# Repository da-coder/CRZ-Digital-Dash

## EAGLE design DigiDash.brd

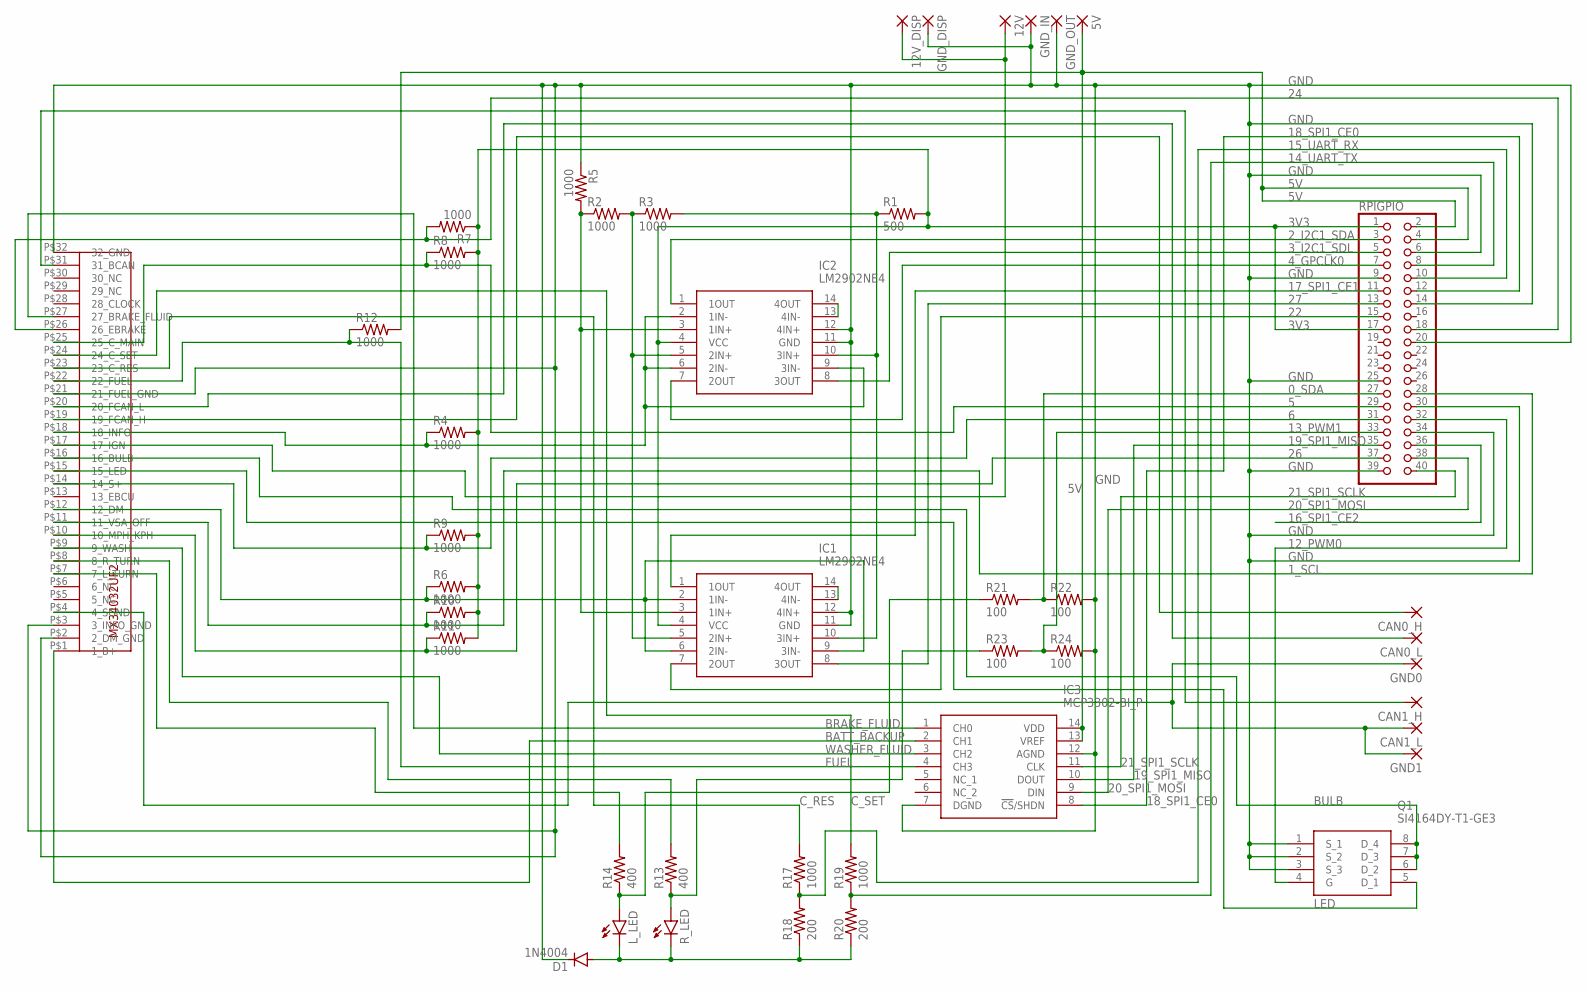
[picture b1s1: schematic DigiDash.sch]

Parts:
5V, 12V, 12V_DISP: 3,81/1,4
CAN0_H, CAN0_L, CAN1_H, CAN1_L: 3,81/1,4
D1: 1N4004; DO41-10
GND0, GND1: 3,81/1,4
GND_DISP: 3,81/1,4
GND_IN: 3,81/1,4
GND_OUT: 3,81/1,4
IC1, IC2: LM2902NE4; DIP794W53P254L1930H508Q14N
IC3: MCP3302-BI_P; DIP781W56P254L1918H533Q14N
L_LED: LED3MM
Q1: SI4164DY-T1-GE3; SOIC127P600X175-8N
R1: 500; 0204/7
R2, R3, R4, R5, R6, R7, R8, R9, R10, R11, R12, R17, R19: 1000; 0204/7
R13, R14: 400; 0204/7
R18, R20: 200; 0204/7
R21, R22, R23, R24: 100; 0204/7
RPIGPIO: PINHD-2X20; 2X20
R_LED: LED3MM
U$1: MX34032UF2

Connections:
0_SDA: R21.2, R22.1, RPIGPIO.27
1_SCL: R10.1, RPIGPIO.28, U$1.P$11 (11_VSA_OFF)
2_I2C1_SDA: IC2.1 (1OUT), RPIGPIO.3
3V3: IC1.4 (VCC), IC2.4 (VCC), R1.2, R4.2, R6.2, R7.1, R8.2, R9.2, R10.2, R11.2, RPIGPIO.1, RPIGPIO.17
3_I2C1_SDL: IC2.8 (3OUT), RPIGPIO.5
4_GPCLK0: IC2.7 (2OUT), RPIGPIO.7
5: R8.1, RPIGPIO.29, U$1.P$25 (25_C_MAIN)
5V: 5V.1, IC3.13 (VREF), IC3.14 (VDD), R12.2, RPIGPIO.2, RPIGPIO.4
6: R9.1, RPIGPIO.31, U$1.P$14 (14_S+)
12_PWM0: Q1.4 (G), RPIGPIO.32
13_PWM1: R23.2, R24.1, RPIGPIO.33
14_UART_TX: R19.1, R20.2, RPIGPIO.8
15_UART_RX: R17.1, R18.2, RPIGPIO.10
16_SPI1_CE2: RPIGPIO.36
17_SPI1_CE1: IC1.1 (1OUT), RPIGPIO.11
18_SPI1_CE0: IC3.8 (!CS!/SHDN), RPIGPIO.12
19_SPI1_MISO: IC3.10 (DOUT), RPIGPIO.35
20_SPI1_MOSI: IC3.9 (DIN), RPIGPIO.38
21_SPI1_SCLK: IC3.11 (CLK), RPIGPIO.40
22: IC1.7 (2OUT), RPIGPIO.15
24: R7.2, RPIGPIO.18, U$1.P$26 (26_EBRAKE)
26: R11.1, RPIGPIO.37, U$1.P$10 (10_MPH_KPH)
27: IC1.8 (3OUT), RPIGPIO.13
BATT_BACKUP: IC3.2 (CH1), U$1.P$1 (1_B+)
BRAKE_FLUID: IC3.1 (CH0), U$1.P$27 (27_BRAKE_FLUID)
BULB: Q1.6 (D_2), Q1.7 (D_3), Q1.8 (D_4), U$1.P$16 (16_BULB)
C_RES: R17.2, U$1.P$23 (23_C_RES)
C_SET: R19.2, U$1.P$24 (24_C_SET)
FUEL: IC3.4 (CH3), R12.1, U$1.P$22 (22_FUEL)
GND: D1.C, GND_DISP.1, GND_IN.1, GND_OUT.1, IC1.11 (GND), IC1.12 (4IN+), IC2.11 (GND), IC2.12 (4IN+), IC3.7 (DGND), IC3.12 (AGND), Q1.1 (S_1), Q1.2 (S_2), Q1.3 (S_3), R5.1, R22.2, R24.2, RPIGPIO.6, RPIGPIO.9, RPIGPIO.14, RPIGPIO.20, RPIGPIO.25, RPIGPIO.30, RPIGPIO.34, RPIGPIO.39, U$1.P$2 (2_DM_GND), U$1.P$3 (3_INFO_GND), U$1.P$21 (21_FUEL_GND), U$1.P$32 (32_GND)
LED: Q1.5 (D_1), U$1.P$15 (15_LED)
unnamed: IC1.2 (1IN-), IC1.6 (2IN-), IC1.9 (3IN-), R6.1, U$1.P$12 (12_DM)
unnamed: R14.2, U$1.P$7 (7_L_TURN)
unnamed: IC1.10 (3IN+), IC2.10 (3IN+), R1.1, R3.2
unnamed: IC1.3 (1IN+), IC2.3 (1IN+), R2.1, R5.2
unnamed: IC2.13 (4IN-), IC2.14 (4OUT)
unnamed: IC1.5 (2IN+), IC2.5 (2IN+), R2.2, R3.1
unnamed: IC1.13 (4IN-), IC1.14 (4OUT)
unnamed: CAN1_H.1, U$1.P$31 (31_BCAN)
unnamed: CAN1_L.1, GND0.1, GND1.1, U$1.P$4 (4_SGND)
unnamed: CAN0_H.1, U$1.P$19 (19_FCAN_H)
unnamed: CAN0_L.1, U$1.P$20 (20_FCAN_L)
unnamed: R13.2, U$1.P$8 (8_R_TURN)
unnamed: IC2.2 (1IN-), IC2.6 (2IN-), IC2.9 (3IN-), R4.1, U$1.P$18 (18_INFO)
unnamed: D1.A, L_LED.K (C), R18.1, R20.1, R_LED.K (C)
unnamed: 12V.1, 12V_DISP.1, U$1.P$17 (17_IGN)
unnamed: R13.1, R23.1, R_LED.A
unnamed: L_LED.A, R14.1, R21.1
WASHER_FLUID: IC3.3 (CH2), U$1.P$9 (9_WASH)

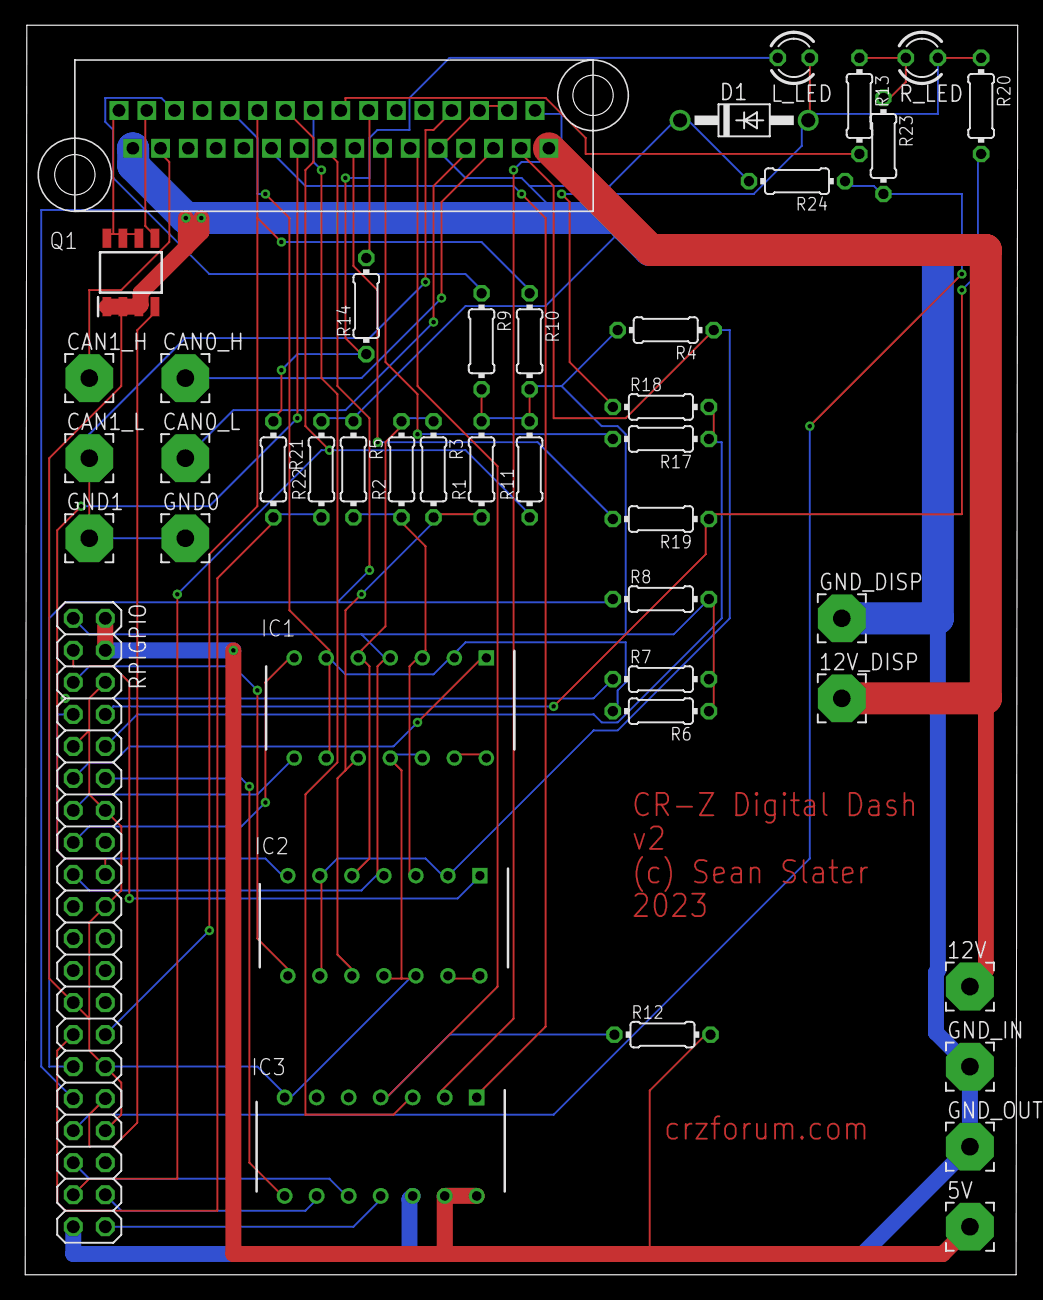
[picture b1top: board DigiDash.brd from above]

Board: 2 copper layers, 78.7 x 99.1 mm, 43 parts (0 on the bottom side), 48 nets.

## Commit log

2024-01-31 moved photos to folder
